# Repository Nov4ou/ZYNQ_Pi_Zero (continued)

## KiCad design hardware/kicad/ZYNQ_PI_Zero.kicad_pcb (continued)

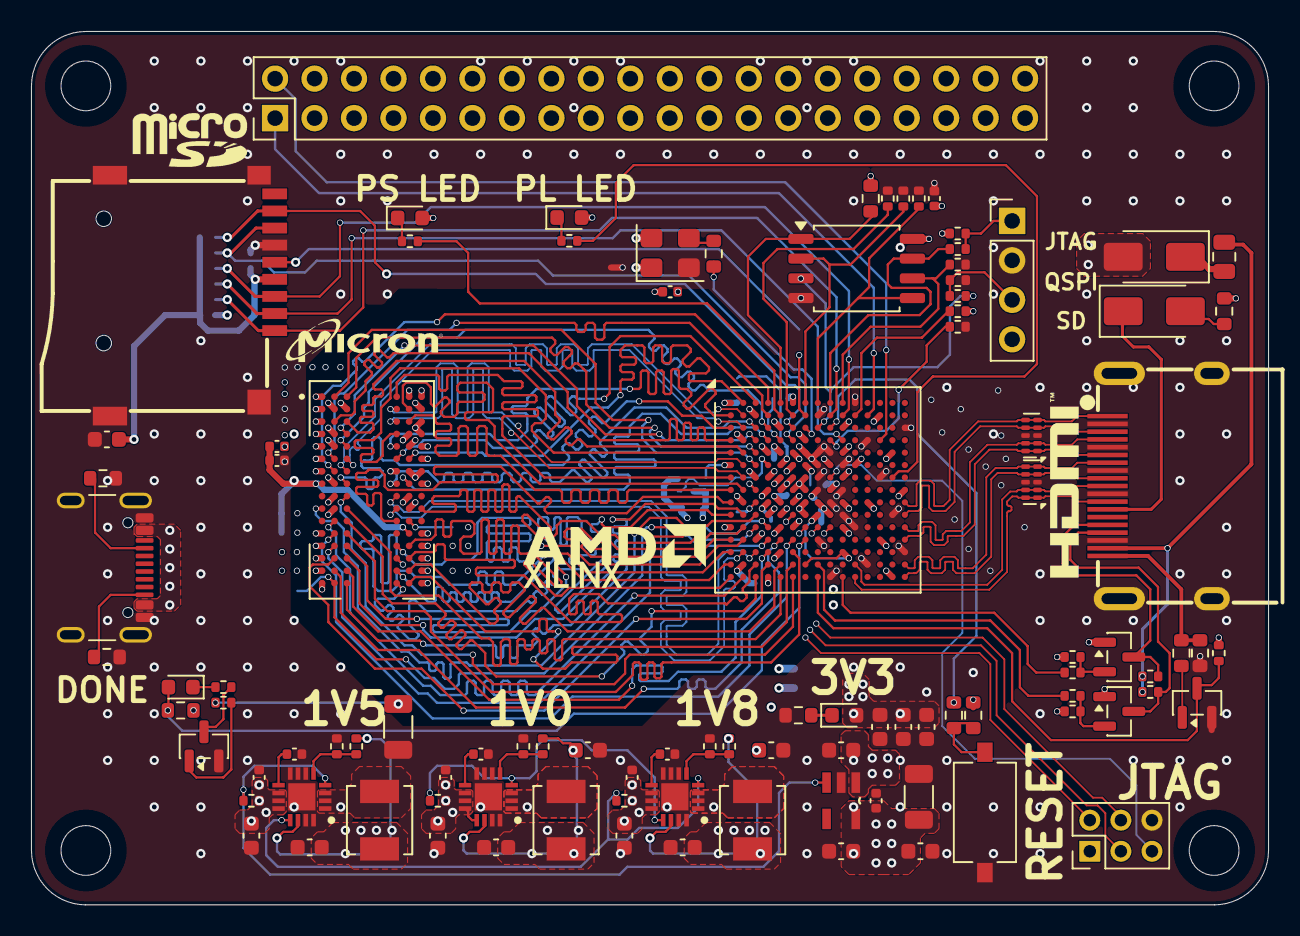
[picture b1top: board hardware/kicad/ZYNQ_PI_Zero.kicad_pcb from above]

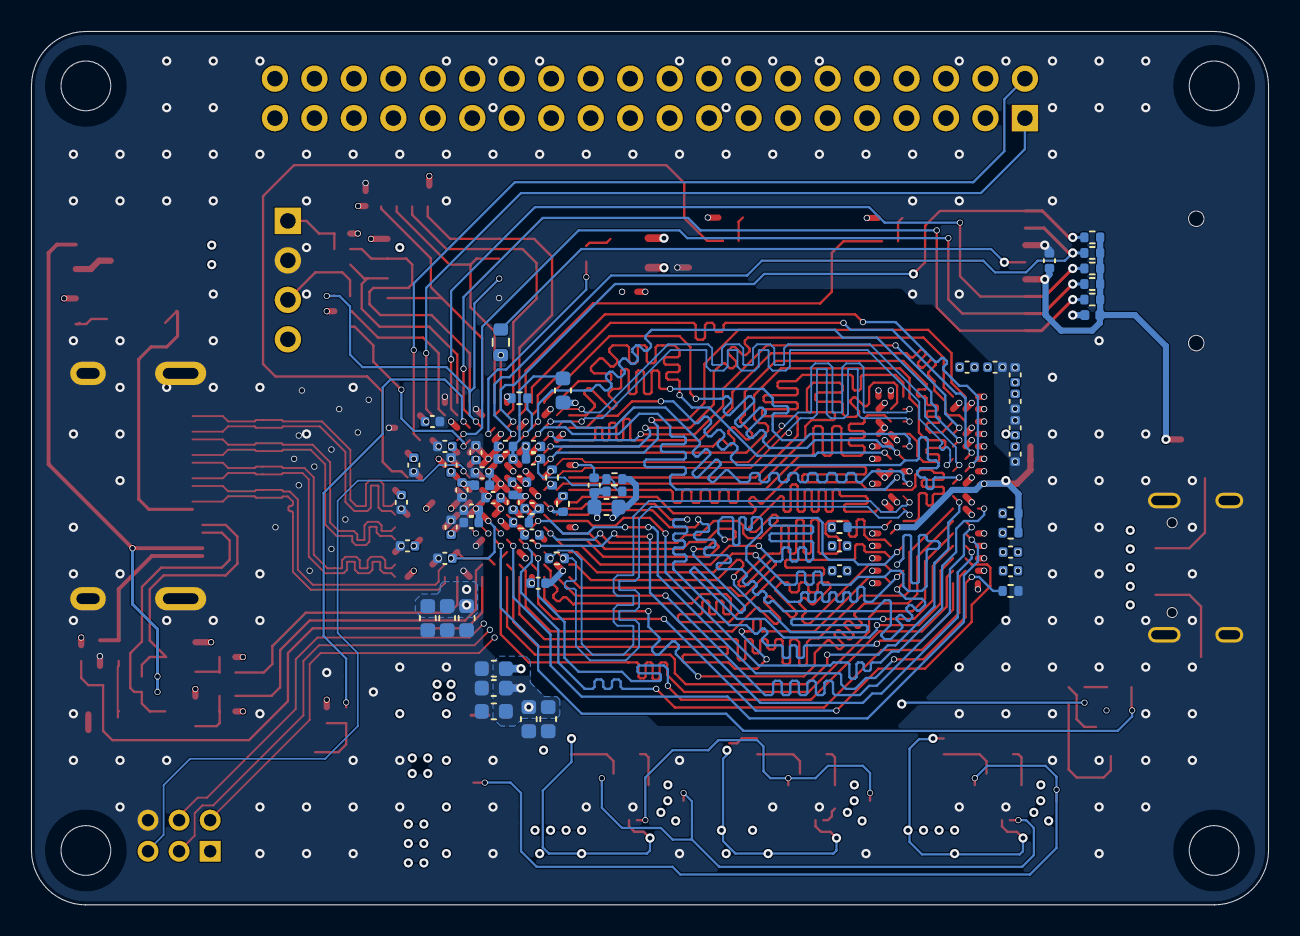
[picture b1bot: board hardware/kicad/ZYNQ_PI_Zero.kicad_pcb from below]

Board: 4 copper layers, 79.6 x 56.2 mm, 168 parts (64 on the bottom side), 137 nets.

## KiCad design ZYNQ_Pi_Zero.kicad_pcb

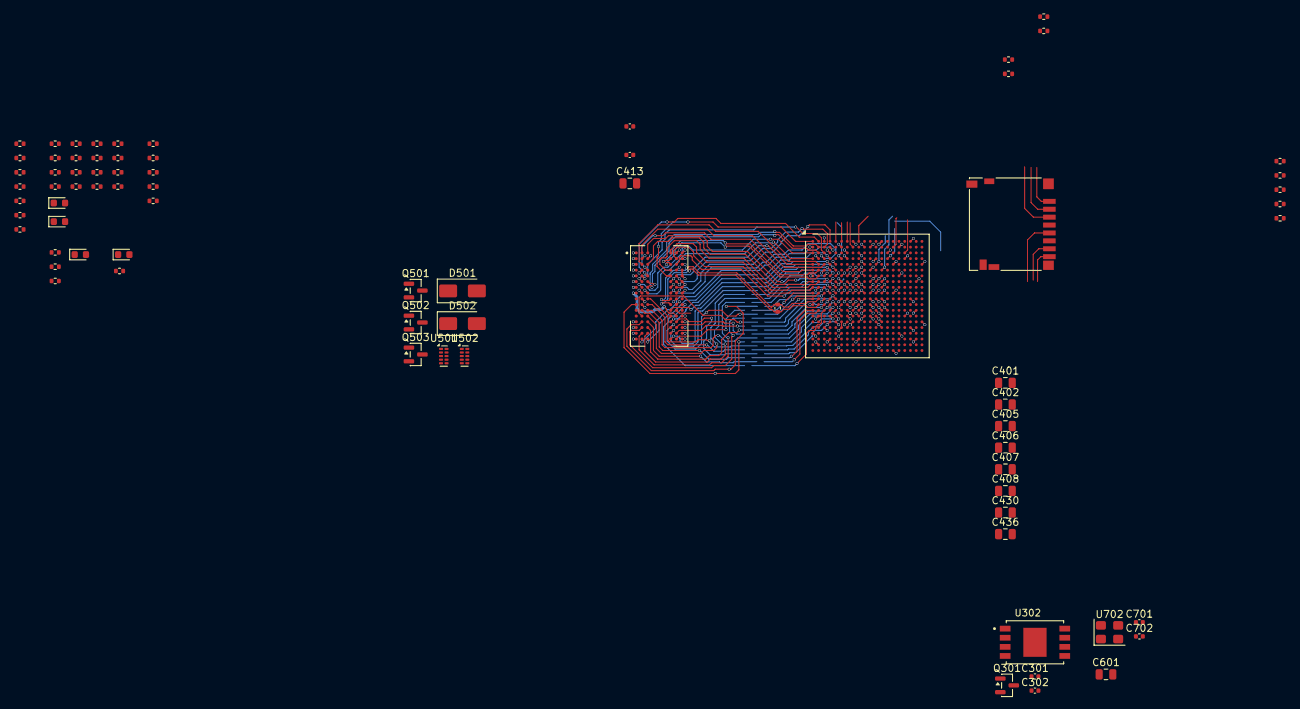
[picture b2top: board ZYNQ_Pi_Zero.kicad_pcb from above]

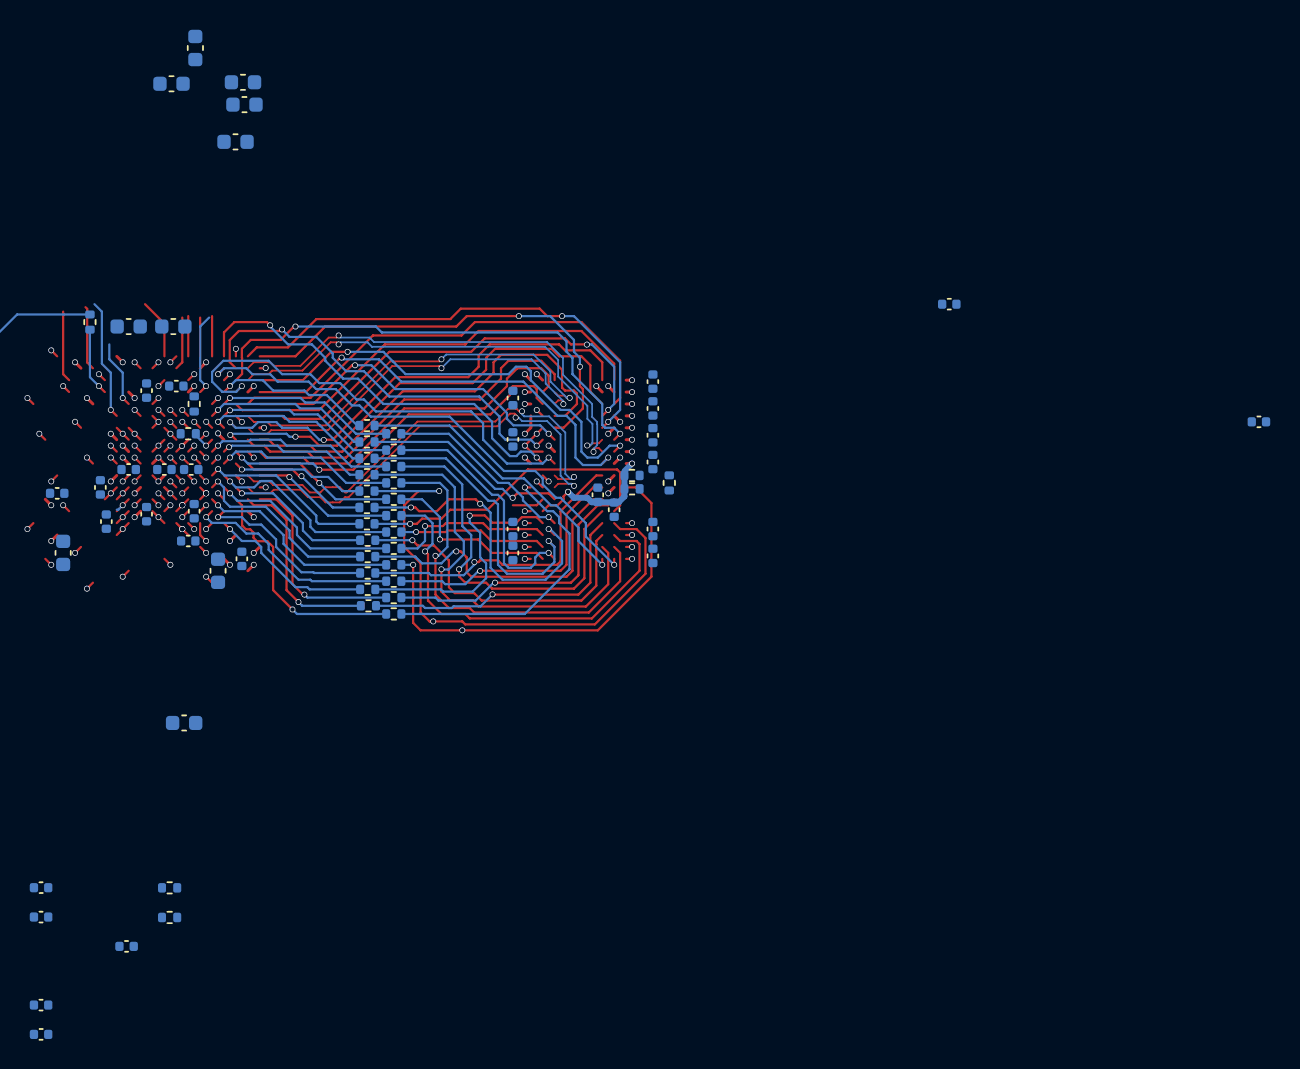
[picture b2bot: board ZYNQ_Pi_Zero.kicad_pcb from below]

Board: 4 copper layers, 148 parts (73 on the bottom side), 124 nets.

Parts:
C201, C202, C203, C204, C205, C206, C207, C208, C209, C210, C211, C212, C214, C303, C415, C602, C701: 100n; C_0402_1005Metric
C213: 10n; C_0402_1005Metric
C301, C302, C411, C412, C418, C419, C422, C423, C424, C427, C428, C429, C431, C434, C435, C702: 470n; C_0402_1005Metric
C401, C402, C406, C408, C413, C430, C601: 10u; C_0805_2012Metric
C403, C404, C414: 3n3; C_0402_1005Metric
C405: 47u; C_0805_2012Metric
C407, C436: 22u; C_0805_2012Metric
C409, C410, C416, C417, C420, C421, C425, C426, C432, C433: 4u7; C_0603_1608Metric
D301, D302, D701, D801: LED; LED_0603_1608Metric
D501, D502: SS14; D_SMA
J601: Micro_SD_Card; microSD_HC_Hirose_DM3D-SF
Q301: MMBT3904; SOT-23
Q501, Q502, Q503: 2N7002; SOT-23
R201: 240R; R_0402_1005Metric
R202, R203, R404, R409, R516, R517: 10k; R_0402_1005Metric
R204, R205, R206: 80R6; R_0402_1005Metric
R207, R208, R209, R210, R211, R212, R213, R214, R215, R216, R217, R218, R219, R220, R221, R222, R223, R224, R225, R226, R227, R228, R229, R230: 10R; R_0402_1005Metric
R301, R303, R701, R708, R709, R801: 1k; R_0402_1005Metric
R302: 330R; R_0402_1005Metric
R304, R305, R506, R508, R513, R514, R518: 4k7; R_0402_1005Metric
R306: 390R; R_0402_1005Metric
R307: 470R; R_0402_1005Metric
R308, R309, R310, R311, R312, R313, R314, R315, R316: 20k; R_0402_1005Metric
R401: 100k; R_0402_1005Metric
R402, R403: 5k1; R_0402_1005Metric
R405: 86k6; R_0402_1005Metric
R406: 200k; R_0402_1005Metric
R407: 13k; R_0402_1005Metric
R408, R411: 15k; R_0402_1005Metric
R410: 18k7; R_0402_1005Metric
R601, R602, R603, R604, R605: 47k; R_0402_1005Metric
R711: 33R; R_0402_1005Metric
U101: xc7z010clg400; Xilinx_CLG400
U201: MT41K256M16TW-107_P; BGA96C80P9X16_1400X800X120
U302: W25Q256FVEI; IC_W25N04KVZEIU
U501, U502: TPD4E05U06DQA; USON-10_2.5x1.0mm_P0.5mm
U702: 33.3333MHz; Oscillator_SMD_SeikoEpson_SG8002CE-4Pin_3.2x2.5mm

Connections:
+1V0: C405.1, C409.1, C411.1, C420.1, C422.1, C424.1, C425.1, C427.1, C429.1, R405.1, U101.G7 (VCCPINT[6]), U101.G11 (VCCBRAM[2]), U101.G13 (VCCINT[9]), U101.H10 (VCCBRAM[2]), U101.H12 (VCCINT[9]), U101.J7 (VCCPINT[6]), U101.J13 (VCCINT[9]), U101.K12 (VCCINT[9]), U101.L7 (VCCPINT[6]), U101.L13 (VCCINT[9]), U101.M12 (VCCINT[9]), U101.N7 (VCCPINT[6]), U101.N13 (VCCINT[9]), U101.P8 (VCCPINT[6]), U101.P12 (VCCINT[9]), U101.R7 (VCCPINT[6]), U101.R13 (VCCINT[9])
+1V5: C201.1, C202.1, C203.1, C204.1, C205.1, C206.1, C207.1, C209.1, C210.1, C211.1, C212.1, C407.1, C433.1, C435.1, R202.1, R204.1, R301.1, R407.1, U101.A3 (VCCO_DDR_502[10]), U101.D2 (VCCO_DDR_502[10]), U101.E5 (VCCO_DDR_502[10]), U101.G1 (VCCO_DDR_502[10]), U101.H4 (VCCO_DDR_502[10]), U101.L3 (VCCO_DDR_502[10]), U101.P2 (VCCO_DDR_502[10]), U101.R5 (VCCO_DDR_502[10]), U101.U1 (VCCO_DDR_502[10]), U101.V4 (VCCO_DDR_502[10]), U201.A1 (VDDQ), U201.A8 (VDDQ), U201.B2 (VDD), U201.C1 (VDDQ), U201.C9 (VDDQ), U201.D2 (VDDQ), U201.D9 (VDD), U201.E9 (VDDQ), U201.F1 (VDDQ), U201.G7 (VDD), U201.H2 (VDDQ), U201.H9 (VDDQ), U201.K2 (VDD), U201.K8 (VDD), U201.N1 (VDD), U201.N9 (VDD), U201.R1 (VDD), U201.R9 (VDD)
+1V8: C416.1, C417.1, C418.1, C419.1, C426.1, C428.1, C432.1, C434.1, C436.1, R410.1, R708.1, U101.A13 (VCCO_MIO1_501[4]), U101.B16 (VCCO_MIO1_501[4]), U101.C19 (VCCO_35[6]), U101.D12 (VCCO_MIO1_501[4]), U101.E15 (VCCO_MIO1_501[4]), U101.F8 (VCCPAUX[5]), U101.F11 (VCCBATT_0), U101.F18 (VCCO_35[6]), U101.G9 (VCCPAUX[5]), U101.H8 (VCCPAUX[5]), U101.H14 (VCCO_35[6]), U101.J11 (VCCAUX[6]), U101.J17 (VCCO_35[6]), U101.K8 (VCCPAUX[5]), U101.K20 (VCCO_35[6]), U101.L11 (VCCAUX[6]), U101.M8 (VCCPAUX[5]), U101.M16 (VCCO_35[6]), U101.N9 (VCCAUX[6]), U101.N11 (VCCAUX[6]), U101.P10 (VCCAUX[6]), U101.R9 (VCCAUX[6])
+3V3: C302.1, C303.1, C410.1, C412.1, C413.1, C415.1, C421.1, C423.1, C701.1, D302.2 (A), D701.2 (A), D801.2 (A), Q501.1 (G), Q502.1 (G), R302.1, R304.1, R305.1, R307.1, R308.1, R313.1, R506.1, R508.1, R518.1, U101.B6 (VCCO_MIO0_500[2]), U101.D7 (VCCO_MIO0_500[2]), U101.K6 (VCCO_0), U101.M6 (CFGBVS_0), U101.N6 (RSVDVCC3), U101.N19 (VCCO_34[6]), U101.R6 (RSVDVCC2), U101.R15 (VCCO_34[6]), U101.T6 (RSVDVCC1), U101.T8 (VCCO_13[4]), U101.T18 (VCCO_34[6]), U101.U11 (VCCO_13[4]), U101.V14 (VCCO_34[6]), U101.W7 (VCCO_13[4]), U101.W17 (VCCO_34[6]), U101.Y10 (VCCO_13[4]), U101.Y20 (VCCO_34[6]), U302.8 (VCC), U702.1 (OE), U702.4 (VDD)
+3V3_SD: C601.1, C602.1, J601.4 (VDD), R601.2, R602.2, R603.2, R604.2, R605.2
+5V: C401.1, C402.1, C406.1, C408.1, D501.2 (A), R401.2, R404.2, R409.2
+HDMI_5V: R513.1, R514.1
/BANK0/INIT_B: R304.2, U101.R10 (INIT_B_0)
/BANK0/PROGRAM_B: R305.2, U101.L6 (PROGRAM_B_0)
/DDR3/DDR_A0: R207.2, U201.N3 (A0)
/DDR3/DDR_A1: R208.2, U201.P7 (A1)
/DDR3/DDR_A2: R209.2, U201.P3 (A2)
/DDR3/DDR_A3: R210.2, U201.N2 (A3)
/DDR3/DDR_A4: R211.2, U201.P8 (A4)
/DDR3/DDR_A5: R212.2, U201.P2 (A5)
/DDR3/DDR_A6: R213.2, U201.R8 (A6)
/DDR3/DDR_A7: R214.2, U201.R2 (A7)
/DDR3/DDR_A8: R215.2, U201.T8 (A8)
/DDR3/DDR_A9: R216.2, U201.R3 (A9)
/DDR3/DDR_A10: R217.2, U201.L7 (A10/AP)
/DDR3/DDR_A11: R218.2, U201.R7 (A11)
/DDR3/DDR_A12: R219.2, U201.N7 (A12/~BC)
/DDR3/DDR_A13: R220.2, U201.T3 (A13)
/DDR3/DDR_A14: R221.2, U201.T7 (A14)
/DDR3/DDR_BA0: R222.2, U201.M2 (BA0)
/DDR3/DDR_BA1: R223.2, U201.N8 (BA1)
/DDR3/DDR_BA2: R224.2, U201.M3 (BA2)
/DDR3/DDR_CKE: R226.2, U201.K9 (CKE)
/DDR3/DDR_CLK_N: R206.1, U101.M2 (PS_DDR_CKN_502), U201.K7 (~CK)
/DDR3/DDR_CLK_P: R206.2, U101.L2 (PS_DDR_CKP_502), U201.J7 (CK)
/DDR3/DDR_D0: U101.C3 (PS_DDR_DQ0_502), U201.F2 (DQ2)
/DDR3/DDR_D1: U101.B3 (PS_DDR_DQ1_502), U201.F8 (DQ3)
/DDR3/DDR_D2: U101.A2 (PS_DDR_DQ2_502), U201.E3 (DQ0)
/DDR3/DDR_D3: U101.A4 (PS_DDR_DQ3_502), U201.H8 (DQ5)
/DDR3/DDR_D4: U101.D3 (PS_DDR_DQ4_502), U201.H7 (DQ7)
/DDR3/DDR_D5: U101.D1 (PS_DDR_DQ5_502), U201.H3 (DQ4)
/DDR3/DDR_D6: U101.C1 (PS_DDR_DQ6_502), U201.G2 (DQ6)
/DDR3/DDR_D7: U101.E1 (PS_DDR_DQ7_502), U201.F7 (DQ1)
/DDR3/DDR_D8: U101.E2 (PS_DDR_DQ8_502), U201.C2 (DQ11)
/DDR3/DDR_D9: U101.E3 (PS_DDR_DQ9_502), U201.A2 (DQ13)
/DDR3/DDR_D10: U101.G3 (PS_DDR_DQ10_502), U201.A3 (DQ15)
/DDR3/DDR_D11: U101.H3 (PS_DDR_DQ11_502), U201.C3 (DQ9)
/DDR3/DDR_D12: U101.J3 (PS_DDR_DQ12_502), U201.C8 (DQ10)
/DDR3/DDR_D13: U101.H2 (PS_DDR_DQ13_502), U201.A7 (DQ12)
/DDR3/DDR_D14: U101.H1 (PS_DDR_DQ14_502), U201.D7 (DQ8)
/DDR3/DDR_D15: U101.J1 (PS_DDR_DQ15_502), U201.B8 (DQ14)
/DDR3/DDR_DM0: U101.A1 (PS_DDR_DM0_502), U201.E7 (LDM)
/DDR3/DDR_DM1: U101.F1 (PS_DDR_DM1_502), U201.D3 (UDM)
/DDR3/DDR_DQS0_N: U101.B2 (PS_DDR_DQS_N0_502), U201.G3 (~LDQS)
/DDR3/DDR_DQS0_P: U101.C2 (PS_DDR_DQS_P0_502), U201.F3 (LDQS)
/DDR3/DDR_DQS1_N: U101.F2 (PS_DDR_DQS_N1_502), U201.B7 (~UDQS)
/DDR3/DDR_DQS1_P: U101.G2 (PS_DDR_DQS_P1_502), U201.C7 (UDQS)
/DDR3/DDR_ODT: R228.2, U201.K1 (ODT)
/DDR3/DDR_~CAS: R225.2, U201.K3 (~CAS)
/DDR3/DDR_~CS: R227.2, U201.L2 (~CS)
/DDR3/DDR_~RAS: R230.2, U201.J3 (~RAS)
/DDR3/DDR_~RESET: U101.B4 (PS_DDR_DRST_B_502), U201.T2 (~RESET)
/DDR3/DDR_~WE: R229.2, U201.L3 (~WE)
/DDR3/PS_DDR_A0: R207.1, U101.N2 (PS_DDR_A0_502)
/DDR3/PS_DDR_A1: R208.1, U101.K2 (PS_DDR_A1_502)
/DDR3/PS_DDR_A2: R209.1, U101.M3 (PS_DDR_A2_502)
/DDR3/PS_DDR_A3: R210.1, U101.K3 (PS_DDR_A3_502)
/DDR3/PS_DDR_A4: R211.1, U101.M4 (PS_DDR_A4_502)
/DDR3/PS_DDR_A5: R212.1, U101.L1 (PS_DDR_A5_502)
/DDR3/PS_DDR_A6: R213.1, U101.L4 (PS_DDR_A6_502)
/DDR3/PS_DDR_A7: R214.1, U101.K4 (PS_DDR_A7_502)
/DDR3/PS_DDR_A8: R215.1, U101.K1 (PS_DDR_A8_502)
/DDR3/PS_DDR_A9: R216.1, U101.J4 (PS_DDR_A9_502)
/DDR3/PS_DDR_A10: R217.1, U101.F5 (PS_DDR_A10_502)
/DDR3/PS_DDR_A11: R218.1, U101.G4 (PS_DDR_A11_502)
/DDR3/PS_DDR_A12: R219.1, U101.E4 (PS_DDR_A12_502)
/DDR3/PS_DDR_A13: R220.1, U101.D4 (PS_DDR_A13_502)
/DDR3/PS_DDR_A14: R221.1, U101.F4 (PS_DDR_A14_502)
/DDR3/PS_DDR_BA0: R222.1, U101.L5 (PS_DDR_BA0_502)
/DDR3/PS_DDR_BA1: R223.1, U101.R4 (PS_DDR_BA1_502)
/DDR3/PS_DDR_BA2: R224.1, U101.J5 (PS_DDR_BA2_502)
/DDR3/PS_DDR_CKE: R226.1, U101.N3 (PS_DDR_CKE_502)
/DDR3/PS_DDR_ODT: R228.1, U101.N5 (PS_DDR_ODT_502)
/DDR3/PS_DDR_~CAS: R225.1, U101.P5 (PS_DDR_CAS_B_502)
/DDR3/PS_DDR_~CS: R227.1, U101.N1 (PS_DDR_CS_B_502)
/DDR3/PS_DDR_~RAS: R230.1, U101.P4 (PS_DDR_RAS_B_502)
/DDR3/PS_DDR_~WE: R229.1, U101.M5 (PS_DDR_WE_B_502)
/HDMI/HDMI_DDC_SCL_5V: Q501.3 (D), R513.2
/HDMI/HDMI_DDC_SDA_5V: Q502.3 (D), R514.2
/HDMI/HDMI_HPD_5V: R516.1, R517.1
DONE: D301.2 (A), R302.2, U101.R11 (DONE_0)
GND: C201.2, C202.2, C203.2, C204.2, C205.2, C206.2, C208.2, C209.2, C210.2, C211.2, C212.2, C213.2, C214.2, C301.2, C302.2, C303.2, C401.2, C402.2, C403.2, C404.2, C405.2, C406.2, C407.2, C408.2, C409.2, C410.2, C411.2, C412.2, C413.2, C414.2, C415.2, C416.2, C417.2, C418.2, C419.2, C420.2, C421.2, C422.2, C423.2, C424.2, C425.2, C426.2, C427.2, C428.2, C429.2, C430.2, C431.2, C432.2, C433.2, C434.2, C435.2, C436.2, C601.2, C602.2, C701.2, C702.2, J601.6 (VSS), J601.SH (SHIELD), Q301.2 (E), Q503.2 (S), R201.2, R203.2, R205.2, R306.2, R309.1, R310.1, R311.1, R312.1, R316.1, R402.2, R403.2, R406.2, R408.2, R411.2, R516.2, R709.2, U101.A8 (GND[59]), U101.A18 (GND[59]), U101.B1 (GND[59]), U101.B11 (GND[59]), U101.C4 (GND[59]), U101.C9 (GND[59]), U101.C14 (GND[59]), U101.D17 (GND[59]), U101.E10 (GND[59]), U101.E20 (GND[59]), U101.F3 (GND[59]), U101.F7 (GND[59]), U101.F10 (RSVDGND), U101.G10 (GND[59]), U101.G12 (GND[59]), U101.G16 (GND[59]), U101.H7 (GND[59]), U101.H9 (GND[59]), U101.H11 (GND[59]), U101.H13 (GND[59]), U101.H19 (GND[59]), U101.J2 (GND[59]), U101.J8 (GND[59]), U101.J10 (GNDADC_0), U101.J12 (GND[59]), U101.K5 (GND[59]), U101.K7 (GND[59]), U101.K9 (VP_0), U101.K10 (VREFN_0), U101.K11 (GND[59]), U101.K13 (GND[59]), U101.K15 (GND[59]), U101.L8 (GND[59]), U101.L9 (VREFP_0), U101.L10 (VN_0), U101.L12 (GND[59]), U101.L18 (GND[59]), U101.M1 (GND[59]), U101.M7 (GND[59]), U101.M9 (DXP_0), U101.M10 (DXN_0), U101.M11 (GND[59]), U101.M13 (GND[59]), U101.N4 (GND[59]), U101.N8 (GND[59]), U101.N10 (GND[59]), U101.N12 (GND[59]), U101.N14 (GND[59]), U101.P7 (GND[59]), U101.P9 (GND[59]), U101.P11 (GND[59]), U101.P13 (GND[59]), U101.P17 (GND[59]), U101.R8 (GND[59]), U101.R12 (GND[59]), U101.R20 (GND[59]), U101.T3 (GND[59]), U101.T7 (GND[59]), U101.T13 (GND[59]), U101.U6 (GND[59]), U101.U16 (GND[59]), U101.V9 (GND[59]), U101.V19 (GND[59]), U101.W2 (GND[59]), U101.W12 (GND[59]), U101.Y5 (GND[59]), U101.Y15 (GND[59]), U201.A9 (VSS), U201.B1 (VSSQ), U201.B3 (VSS), U201.B9 (VSSQ), U201.D1 (VSSQ), U201.D8 (VSSQ), U201.E1 (VSS), U201.E2 (VSSQ), U201.E8 (VSSQ), U201.F9 (VSSQ), U201.G1 (VSSQ), U201.G8 (VSS), U201.G9 (VSSQ), U201.J2 (VSS), U201.J8 (VSS), U201.M1 (VSS), U201.M9 (VSS), U201.P1 (VSS), U201.P9 (VSS), U201.T1 (VSS), U201.T9 (VSS), U302.4 (GND), U501.3 (GND), U501.8 (GND), U502.3 (GND), U502.8 (GND), U702.2 (GND)
HDMI_HPD_N_3V3: Q503.3 (D), R518.2
unnamed: D301.1 (K), R303.1
unnamed: D302.1 (K), R306.1
unnamed: D701.1 (K), R701.1
unnamed: D801.1 (K), R801.1
unnamed: R313.2, R314.2
unnamed: R315.2, R316.2
unnamed: Q301.1 (B), R301.2
unnamed: Q301.3 (C), R303.2
unnamed: Q501.2 (S), R506.2
unnamed: Q502.2 (S), R508.2
unnamed: Q503.1 (G), R517.2
unnamed: C301.1, U101.J9 (VCCADC_0)
unnamed: R711.2, U101.D14 (PS_MIO40_501)
unnamed: C702.1, R708.2, R709.1, U101.E11 (PS_MIO_VREF_501)
unnamed: R204.2, U101.G5 (PS_DDR_VRN_502)
unnamed: R205.1, U101.H5 (PS_DDR_VRP_502)
unnamed: C430.1, C431.1, U101.G8 (VCCPLL)
unnamed: R201.1, U201.L8 (ZQ)
unnamed: R405.2, R406.1
unnamed: R407.2, R408.1
unnamed: R410.2, R411.1
PS_MIO7: R312.2, U101.D8 (PS_MIO7_500)
PS_MIO8: R308.2, U101.D5 (PS_MIO8_500)
QSPI_CLK: R311.2, U302.6 (CLK)
QSPI_CS: R307.2, U101.A7 (PS_MIO1_500), U302.1 (/CS)
QSPI_D0: R309.2, U101.B8 (PS_MIO2_500), U302.5 (DI(IO0))
QSPI_D1: R310.2, U101.D6 (PS_MIO3_500), U302.2 (D0(IO1))
QSPI_D2_PS_MIO4: R315.1, U101.B7 (PS_MIO4_500), U302.3 (/WP(IO2))
QSPI_D3_PS_MIO5: R314.1, U101.A6 (PS_MIO5_500), U302.7 (/HOLD(IO3))
SD_CLK: J601.5 (CLK), R711.1
SD_CMD: J601.3 (CMD), R605.1, U101.C17 (PS_MIO41_501)
SD_DATA0: J601.7 (DAT0), R601.1, U101.E12 (PS_MIO42_501)
SD_DATA1: J601.8 (DAT1), R602.1, U101.A9 (PS_MIO43_501)
SD_DATA2: J601.1 (DAT2), R603.1, U101.F13 (PS_MIO44_501)
SD_DATA3: J601.2 (DAT3/CD), R604.1, U101.B15 (PS_MIO45_501)
VTTREF: C207.2, C208.1, C213.1, C214.1, R202.2, R203.1, U101.H6 (PS_DDR_VREF0_502), U101.P6 (PS_DDR_VREF1_502), U201.H1 (VREFDQ), U201.M8 (VREFCA)

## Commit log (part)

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2026-05-07 feat: finish ddr3 schematic design
2026-05-08 feat: finish bank0 & qspi sch design
2026-05-09 feat: finish basic power sch design
2026-05-13 feat: finish basic hdmi sch design
2026-05-28 feat: finish ddr3 sch design
2026-05-28 feat: start to routing DDR3
2026-05-29 feat: continue to routing DDR3
2026-05-29 feat: restart routing ddr
2026-05-29 feat: continue routing dd3
2026-05-31 feat: continue routing ddr3
2026-05-31 feat: continue routing ddr
2026-06-02 feat: rerouting ddr
2026-06-02 feat: add serial res
2026-06-02 feat: finish basic ddr3 routing
2026-06-03 feat: modify sch design
2026-06-03 feat: continue sch design
2026-06-04 feat: continue routing
2026-06-05 feat: add sd card footprint
